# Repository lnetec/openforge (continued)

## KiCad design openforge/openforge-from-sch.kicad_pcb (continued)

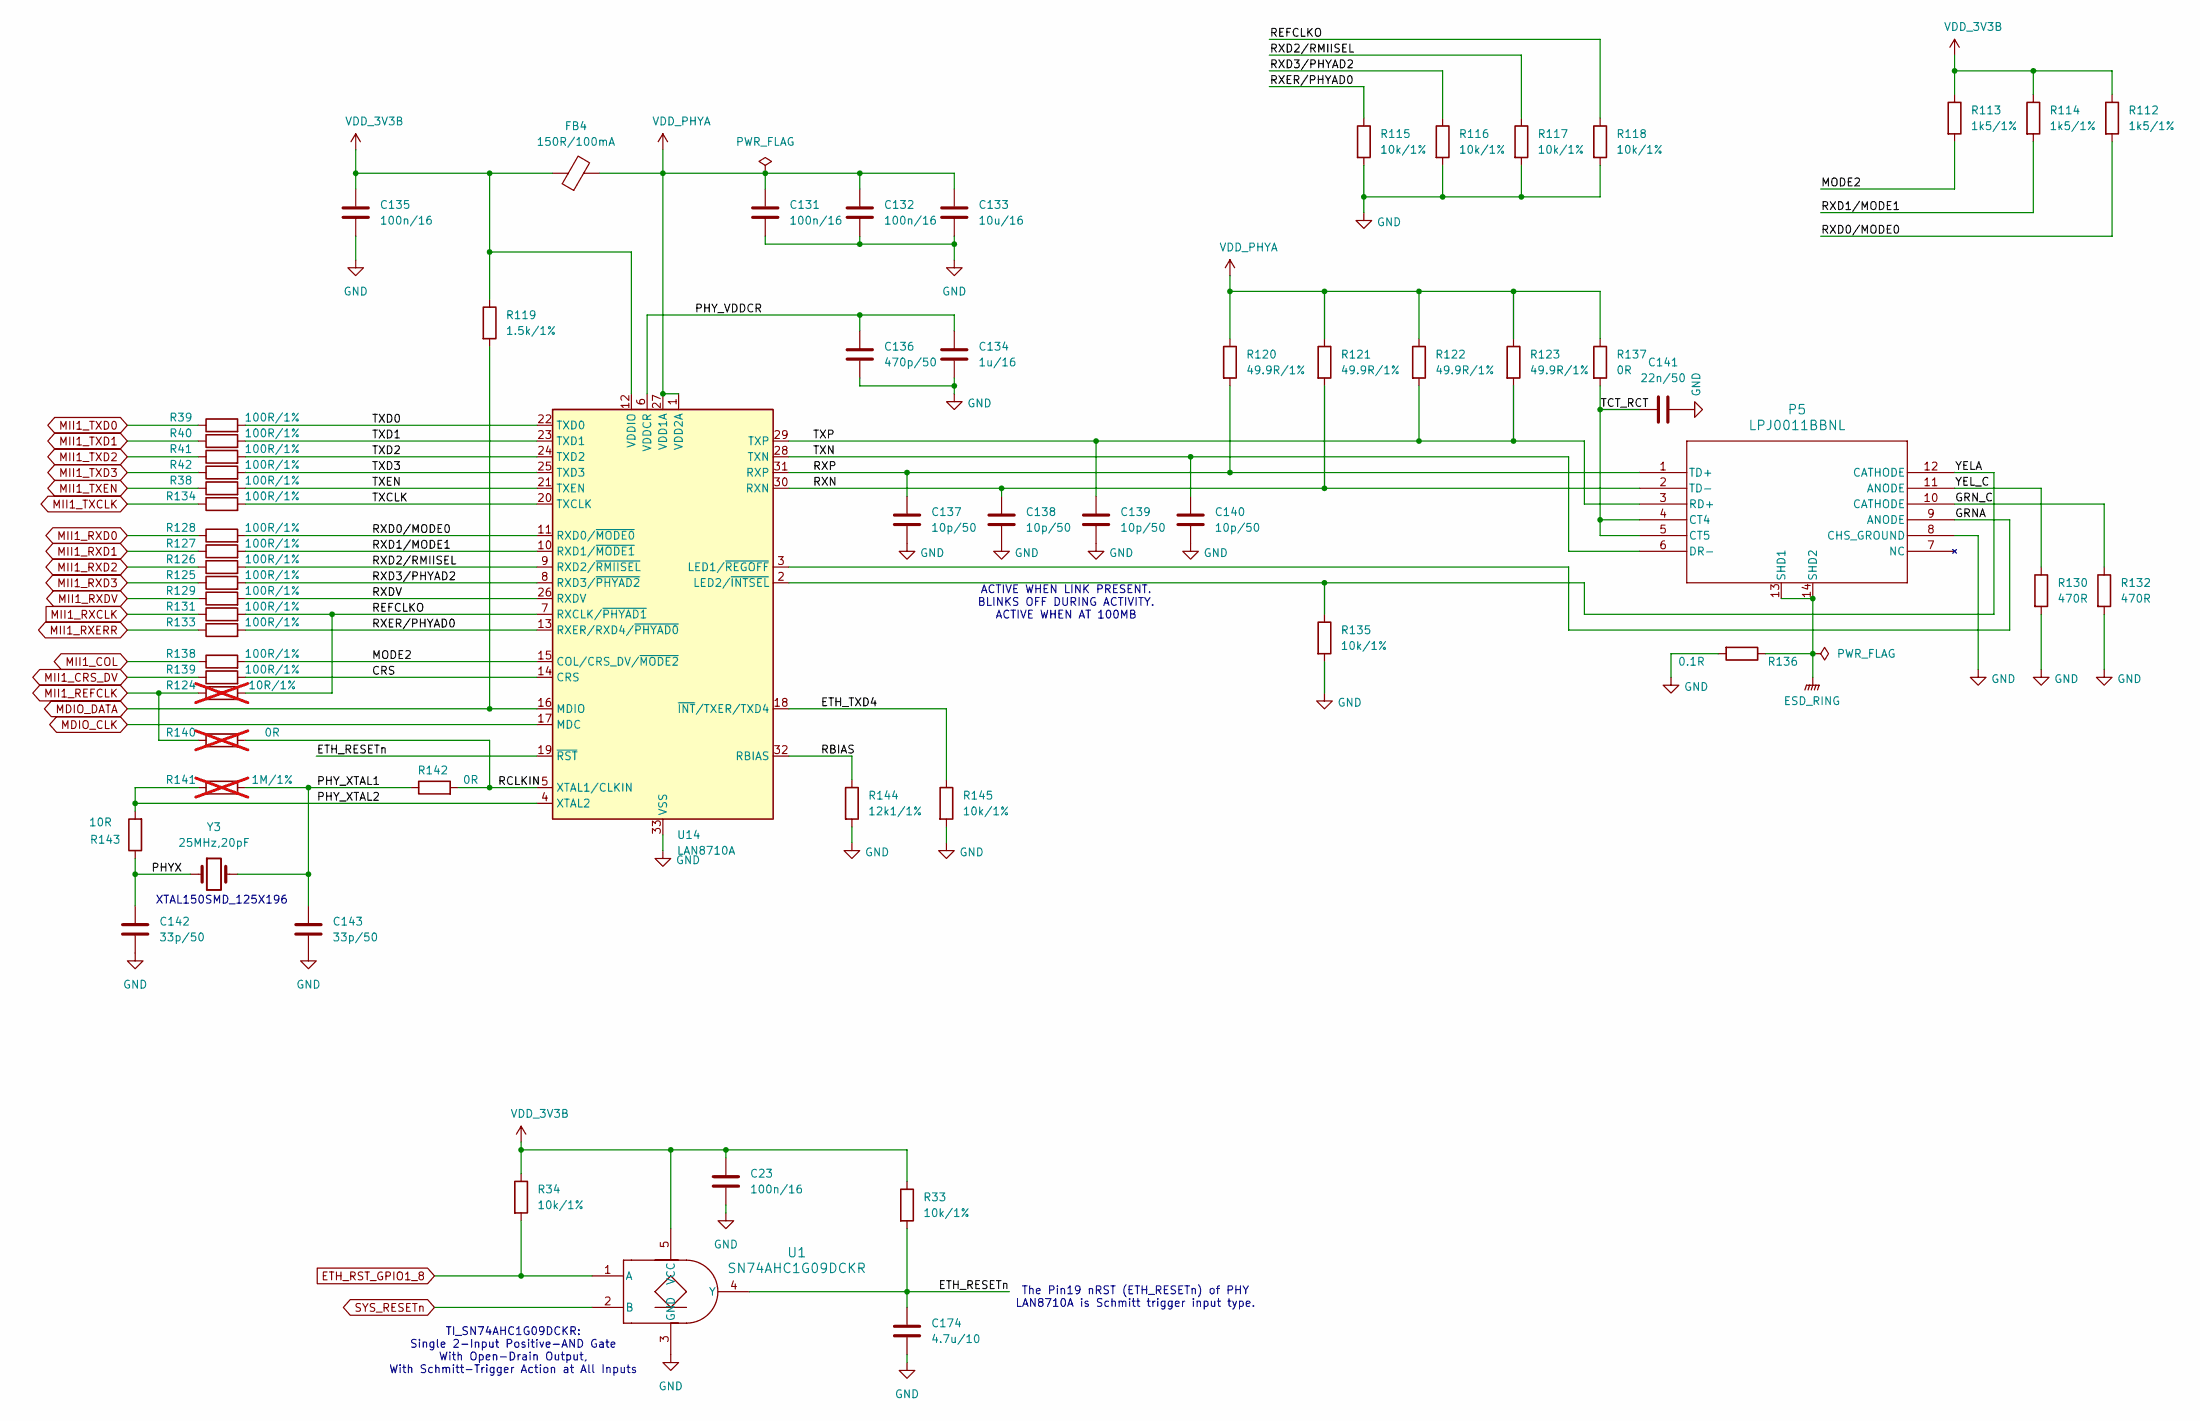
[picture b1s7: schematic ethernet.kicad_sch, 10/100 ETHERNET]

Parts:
C23, C131, C132, C135: 100n/16; C_0402_1005Metric
C133: 10u/16; C_0805_2012Metric
C134: 1u/16; C_0402_1005Metric
C136: 470p/50; C_0402_1005Metric
C137, C138, C139, C140: 10p/50; C_0402_1005Metric
C141: 22n/50; C_0402_1005Metric
C142, C143: 33p/50; C_0402_1005Metric
C174: 4.7u/10; C_0402_1005Metric
FB4: 150R/100mA; L_0805_2012Metric
P5: LPJ0011BBNL; LPJ0011BBNL_LPP
R33, R34, R115, R116, R117, R118, R135, R145: 10k/1%; R_0402_1005Metric
R38, R39, R40, R41, R42, R125, R126, R127, R128, R129, R131, R133, R134, R138, R139: 100R/1%; R_0402_1005Metric
R112, R113, R114: 1k5/1%; R_0402_1005Metric
R119: 1.5k/1%; R_0402_1005Metric
R120, R121, R122, R123: 49.9R/1%; R_0402_1005Metric
R124: 10R/1%; R_0402_1005Metric; not fitted
R130, R132: 470R; R_0402_1005Metric
R136: 0.1R; R_0402_1005Metric
R137, R142: 0R; R_0402_1005Metric
R140: 0R; R_0402_1005Metric; not fitted
R141: 1M/1%; R_0402_1005Metric; not fitted
R143: 10R; R_0402_1005Metric
R144: 12k1/1%; R_0402_1005Metric
U1: SN74AHC1G09DCKR; DCK0005A_L
U14: LAN8710A; QFN-32-1EP_5x5mm_P0.5mm_EP3.3x3.3mm_ThermalVias
Y3: 25MHz,20pF; Crystal_SMD_Abracon_ABM7-2Pin_6.0x3.5mm

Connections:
/Ethernet/CRS: R139.2, U14.14 (CRS)
/Ethernet/ETH_RESETn: C174.1, R33.2, U1.4 (Y), U14.19 (~RST)
/Ethernet/ETH_TXD4: R145.1, U14.18 (~INT/TXER/TXD4)
/Ethernet/GRNA: P5.9 (ANODE), U14.3 (LED1/~REGOFF)
/Ethernet/GRN_C: P5.10 (CATHODE), R132.1
/Ethernet/MODE2: R113.2, R138.2, U14.15 (COL/CRS_DV/~MODE2)
/Ethernet/PHYX: C142.1, R143.1, Y3.1
/Ethernet/PHY_VDDCR: C134.1, C136.1, U14.6 (VDDCR)
/Ethernet/PHY_XTAL1: C143.1, R141.2, R142.1, Y3.2
/Ethernet/PHY_XTAL2: R141.1, R143.2, U14.4 (XTAL2)
/Ethernet/RBIAS: R144.1, U14.32 (RBIAS)
/Ethernet/RCLKIN: R140.2, R142.2, U14.5 (XTAL1/CLKIN)
/Ethernet/REFCLKO: R118.1, R124.2, R131.2, U14.7 (RXCLK/~PHYAD1)
/Ethernet/RXD0/MODE0: R112.2, R128.2, U14.11 (RXD0/~MODE0)
/Ethernet/RXD1/MODE1: R114.2, R127.2, U14.10 (RXD1/~MODE1)
/Ethernet/RXD2/RMIISEL: R117.1, R126.2, U14.9 (RXD2/~RMIISEL)
/Ethernet/RXD3/PHYAD2: R116.1, R125.2, U14.8 (RXD3/~PHYAD2)
/Ethernet/RXDV: R129.2, U14.26 (RXDV)
/Ethernet/RXER/PHYAD0: R115.1, R133.2, U14.13 (RXER/RXD4/~PHYAD0)
/Ethernet/RXN: C138.1, P5.2 (TD-), R121.2, U14.30 (RXN)
/Ethernet/RXP: C137.1, P5.1 (TD+), R120.2, U14.31 (RXP)
/Ethernet/TCT_RCT: C141.1, P5.4 (CT4), P5.5 (CT5), R137.2
/Ethernet/TXCLK: R134.2, U14.20 (TXCLK)
/Ethernet/TXD0: R39.2, U14.22 (TXD0)
/Ethernet/TXD1: R40.2, U14.23 (TXD1)
/Ethernet/TXD2: R41.2, U14.24 (TXD2)
/Ethernet/TXD3: R42.2, U14.25 (TXD3)
/Ethernet/TXEN: R38.2, U14.21 (TXEN)
/Ethernet/TXN: C140.1, P5.6 (DR-), U14.28 (TXN)
/Ethernet/TXP: C139.1, P5.3 (RD+), R122.2, R123.2, U14.29 (TXP)
/Ethernet/YELA: P5.12 (CATHODE), R135.1, U14.2 (LED2/~INTSEL)
/Ethernet/YEL_C: P5.11 (ANODE), R130.1
ESD_RING: P5.13 (SHD1), P5.14 (SHD2), R136.1
ETH_RST_GPIO1_8: R34.2, U1.1 (A); also elsewhere on the board
GND: C23.2, C131.2, C132.2, C133.2, C134.2, C135.2, C136.2, C137.2, C138.2, C139.2, C140.2, C141.2, C142.2, C143.2, C174.2, P5.8 (CHS_GROUND), R115.2, R116.2, R117.2, R118.2, R130.2, R132.2, R135.2, R136.2, R144.2, R145.2, U1.3 (GND), U14.33 (VSS); also elsewhere on the board
MDIO_CLK: U14.17 (MDC); also elsewhere on the board
MDIO_DATA: R119.2, U14.16 (MDIO); also elsewhere on the board
MII1_COL: R138.1; also elsewhere on the board
MII1_CRS_DV: R139.1; also elsewhere on the board
MII1_REFCLK: R124.1, R140.1; also elsewhere on the board
MII1_RXCLK: R131.1; also elsewhere on the board
MII1_RXD0: R128.1; also elsewhere on the board
MII1_RXD1: R127.1; also elsewhere on the board
MII1_RXD2: R126.1; also elsewhere on the board
MII1_RXD3: R125.1; also elsewhere on the board
MII1_RXDV: R129.1; also elsewhere on the board
MII1_RXERR: R133.1; also elsewhere on the board
MII1_TXCLK: R134.1; also elsewhere on the board
MII1_TXD0: R39.1; also elsewhere on the board
MII1_TXD1: R40.1; also elsewhere on the board
MII1_TXD2: R41.1; also elsewhere on the board
MII1_TXD3: R42.1; also elsewhere on the board
MII1_TXEN: R38.1; also elsewhere on the board
SYS_RESETn: U1.2 (B); also elsewhere on the board
VDD_3V3B: C23.1, C135.1, FB4.1, R33.1, R34.1, R112.1, R113.1, R114.1, R119.1, U1.5 (VCC), U14.12 (VDDIO); also elsewhere on the board
VDD_PHYA: C131.1, C132.1, C133.1, FB4.2, R120.1, R121.1, R122.1, R123.1, R137.1, U14.1 (VDD2A), U14.27 (VDD1A)

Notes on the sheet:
The Pin19 nRST (ETH_RESETn) of PHY LAN8710A is Schmitt trigger input type.
TI_SN74AHC1G09DCKR: Single 2-Input Positive-AND Gate With Open-Drain Output, With Schmitt-Trigger Action at All Inputs
ACTIVE WHEN LINK PRESENT. BLINKS OFF DURING ACTIVITY. ACTIVE WHEN AT 100MB
XTAL150SMD_125X196

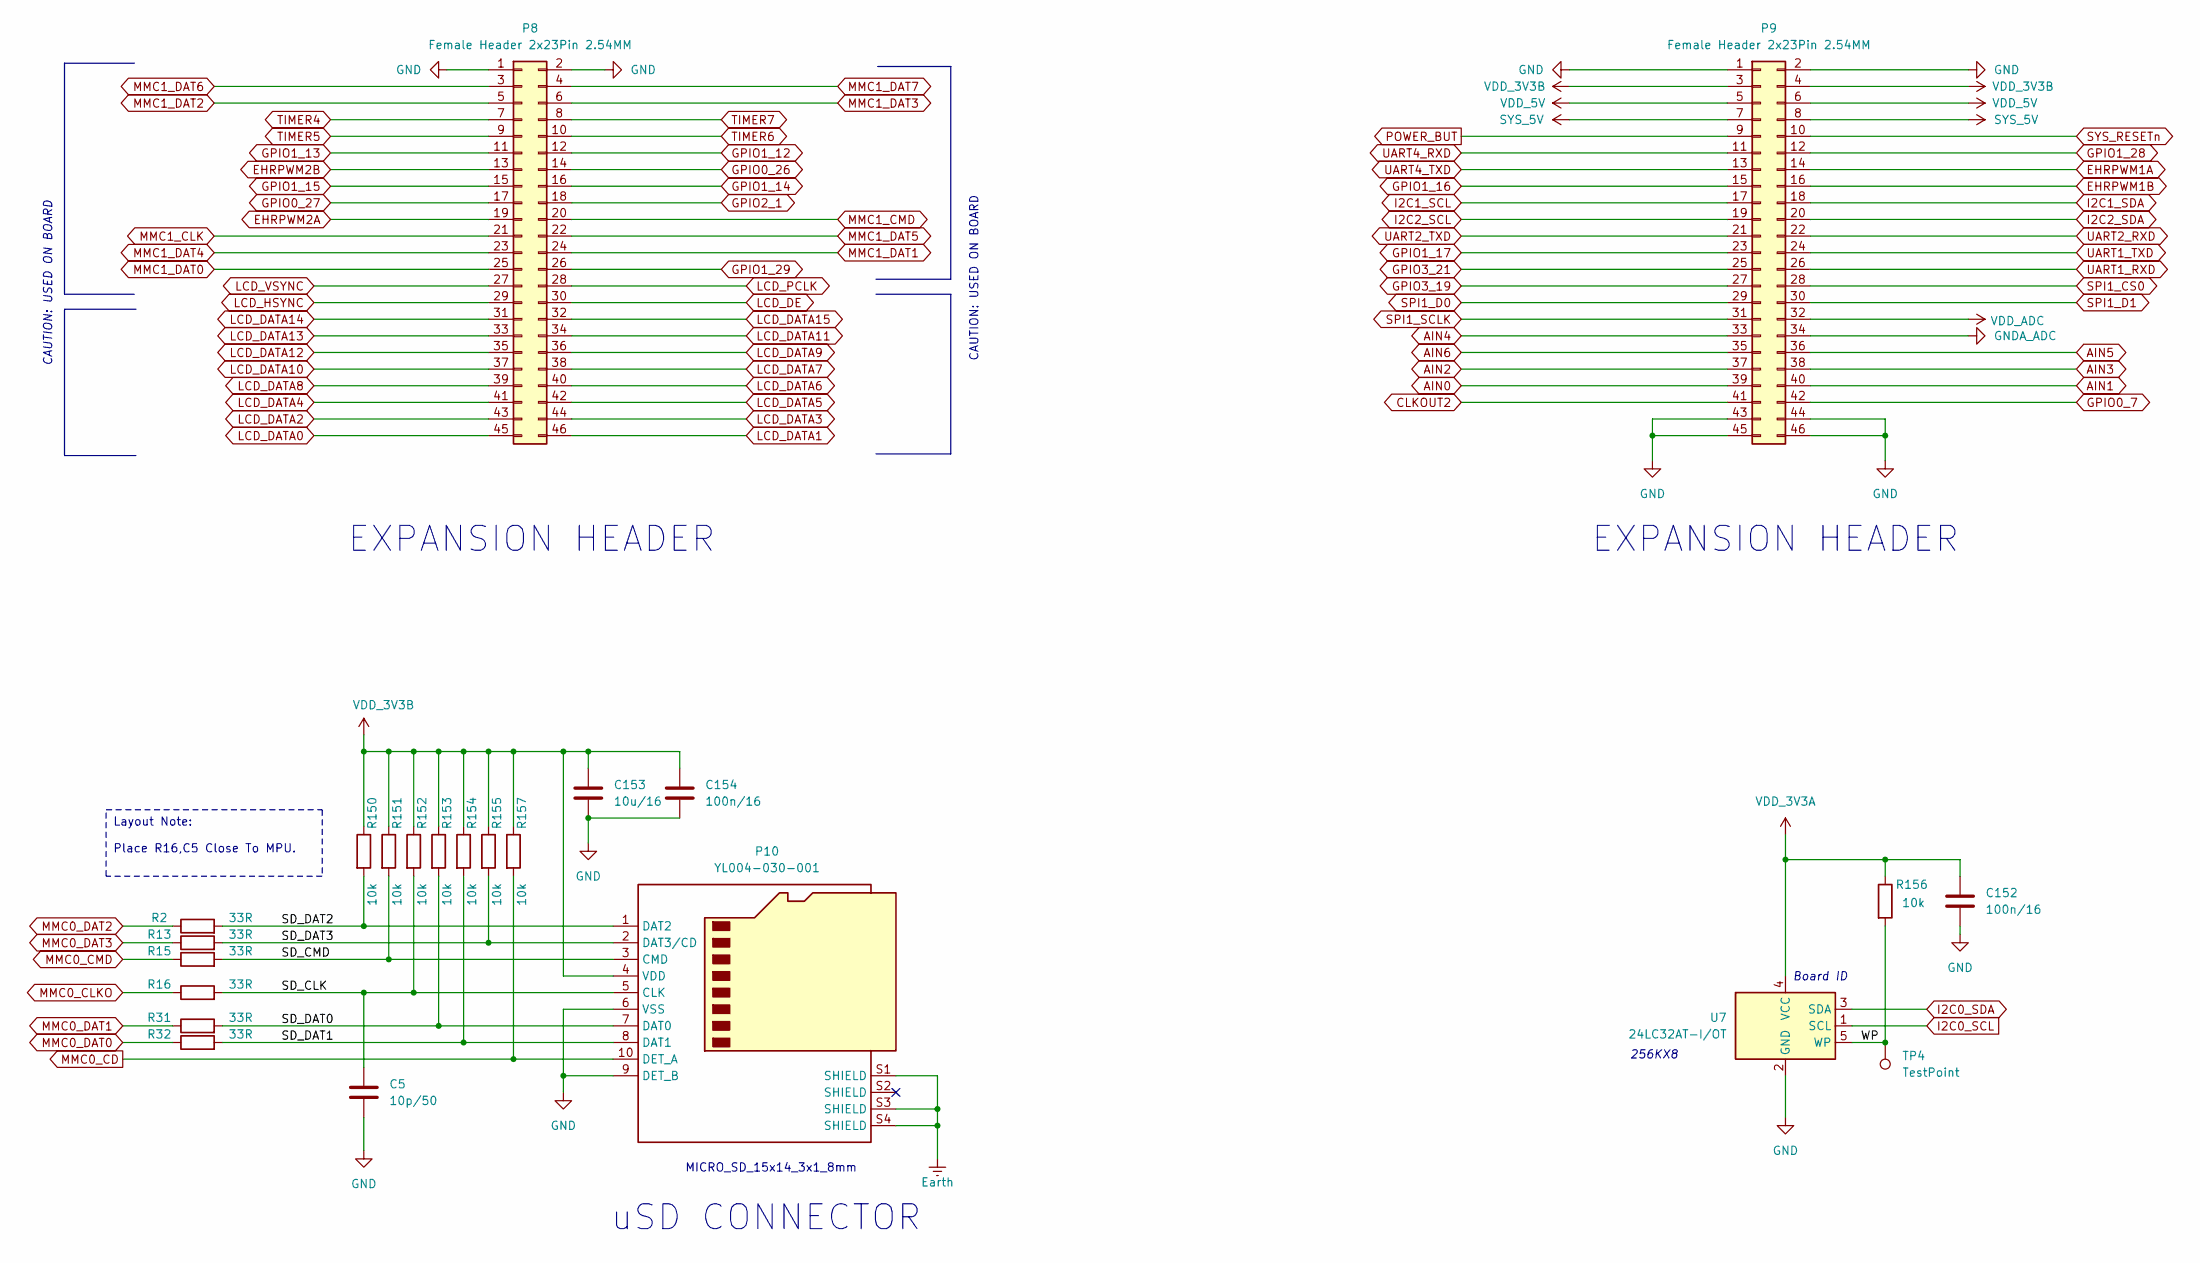
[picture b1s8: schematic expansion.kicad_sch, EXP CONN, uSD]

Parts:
C5: 10p/50; C_0402_1005Metric
C152, C154: 100n/16; C_0402_1005Metric
C153: 10u/16; C_0805_2012Metric
P8, P9: Female Header 2x23Pin 2.54MM; PinHeader_2x23_P2.54mm_Vertical
P10: YL004-030-001; yl004-030-001
R2, R13, R15, R16, R31, R32: 33R; R_0402_1005Metric
R150, R151, R152, R153, R154, R155, R156, R157: 10k; R_0402_1005Metric
TP4: TestPoint; TestPoint_Pad_1.5x1.5mm
U7: 24LC32AT-I/OT; SOT-23-5

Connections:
/Expansion Headers, uSD and EEPROM/SD_CLK: C5.1, P10.5 (CLK), R16.2, R152.2
/Expansion Headers, uSD and EEPROM/SD_CMD: P10.3 (CMD), R15.2, R151.2
/Expansion Headers, uSD and EEPROM/SD_DAT0: P10.7 (DAT0), R31.2, R153.2
/Expansion Headers, uSD and EEPROM/SD_DAT1: P10.8 (DAT1), R32.2, R154.2
/Expansion Headers, uSD and EEPROM/SD_DAT2: P10.1 (DAT2), R2.2, R150.2
/Expansion Headers, uSD and EEPROM/SD_DAT3: P10.2 (DAT3/CD), R13.2, R155.2
/Expansion Headers, uSD and EEPROM/WP: R156.2, TP4.1, U7.5 (WP)
AIN0: P9.39; also elsewhere on the board
AIN1: P9.40; also elsewhere on the board
AIN2: P9.37; also elsewhere on the board
AIN3: P9.38; also elsewhere on the board
AIN4: P9.33; also elsewhere on the board
AIN5: P9.36; also elsewhere on the board
AIN6: P9.35; also elsewhere on the board
CLKOUT2: P9.41; also elsewhere on the board
EHRPWM1A: P9.14; also elsewhere on the board
EHRPWM1B: P9.16; also elsewhere on the board
EHRPWM2A: P8.19; also elsewhere on the board
EHRPWM2B: P8.13; also elsewhere on the board
Earth: P10.S1 (SHIELD), P10.S3 (SHIELD), P10.S4 (SHIELD); also elsewhere on the board
GND: C5.2, C152.2, C153.2, C154.2, P8.1, P8.2, P9.1, P9.2, P9.43, P9.44, P9.45, P9.46, P10.6 (VSS), P10.9 (DET_B), U7.2 (GND); also elsewhere on the board
GNDA_ADC: P9.34; also elsewhere on the board
GPIO0_7: P9.42; also elsewhere on the board
GPIO0_26: P8.14; also elsewhere on the board
GPIO0_27: P8.17; also elsewhere on the board
GPIO1_12: P8.12; also elsewhere on the board
GPIO1_13: P8.11; also elsewhere on the board
GPIO1_14: P8.16; also elsewhere on the board
GPIO1_15: P8.15; also elsewhere on the board
GPIO1_16: P9.15; also elsewhere on the board
GPIO1_17: P9.23; also elsewhere on the board
GPIO1_28: P9.12; also elsewhere on the board
GPIO1_29: P8.26; also elsewhere on the board
GPIO2_1: P8.18; also elsewhere on the board
GPIO3_19: P9.27; also elsewhere on the board
GPIO3_21: P9.25; also elsewhere on the board
I2C0_SCL: U7.1 (SCL); also elsewhere on the board
I2C0_SDA: U7.3 (SDA); also elsewhere on the board
I2C1_SCL: P9.17; also elsewhere on the board
I2C1_SDA: P9.18; also elsewhere on the board
I2C2_SCL: P9.19; also elsewhere on the board
I2C2_SDA: P9.20; also elsewhere on the board
LCD_DATA0: P8.45; also elsewhere on the board
LCD_DATA1: P8.46; also elsewhere on the board
LCD_DATA2: P8.43; also elsewhere on the board
LCD_DATA3: P8.44; also elsewhere on the board
LCD_DATA4: P8.41; also elsewhere on the board
LCD_DATA5: P8.42; also elsewhere on the board
LCD_DATA6: P8.40; also elsewhere on the board
LCD_DATA7: P8.38; also elsewhere on the board
LCD_DATA8: P8.39; also elsewhere on the board
LCD_DATA9: P8.36; also elsewhere on the board
LCD_DATA10: P8.37; also elsewhere on the board
LCD_DATA11: P8.34; also elsewhere on the board
LCD_DATA12: P8.35; also elsewhere on the board
LCD_DATA13: P8.33; also elsewhere on the board
LCD_DATA14: P8.31; also elsewhere on the board
LCD_DATA15: P8.32; also elsewhere on the board
LCD_DE: P8.30; also elsewhere on the board
LCD_HSYNC: P8.29; also elsewhere on the board
LCD_PCLK: P8.28; also elsewhere on the board
LCD_VSYNC: P8.27; also elsewhere on the board
MMC0_CD: P10.10 (DET_A), R157.2; also elsewhere on the board
MMC0_CLKO: R16.1; also elsewhere on the board
MMC0_CMD: R15.1; also elsewhere on the board
MMC0_DAT0: R32.1; also elsewhere on the board
MMC0_DAT1: R31.1; also elsewhere on the board
MMC0_DAT2: R2.1; also elsewhere on the board
MMC0_DAT3: R13.1; also elsewhere on the board
MMC1_CLK: P8.21; also elsewhere on the board
MMC1_CMD: P8.20; also elsewhere on the board
MMC1_DAT0: P8.25; also elsewhere on the board
MMC1_DAT1: P8.24; also elsewhere on the board
MMC1_DAT2: P8.5; also elsewhere on the board
MMC1_DAT3: P8.6; also elsewhere on the board
MMC1_DAT4: P8.23; also elsewhere on the board
MMC1_DAT5: P8.22; also elsewhere on the board
MMC1_DAT6: P8.3; also elsewhere on the board
MMC1_DAT7: P8.4; also elsewhere on the board
POWER_BUT: P9.9; also elsewhere on the board
SPI1_CS0: P9.28; also elsewhere on the board
SPI1_D0: P9.29; also elsewhere on the board
SPI1_D1: P9.30; also elsewhere on the board
SPI1_SCLK: P9.31; also elsewhere on the board
SYS_5V: P9.7, P9.8; also elsewhere on the board
SYS_RESETn: P9.10; also elsewhere on the board
TIMER4: P8.7; also elsewhere on the board
TIMER5: P8.9; also elsewhere on the board
TIMER6: P8.10; also elsewhere on the board
TIMER7: P8.8; also elsewhere on the board
UART1_RXD: P9.26; also elsewhere on the board
UART1_TXD: P9.24; also elsewhere on the board
UART2_RXD: P9.22; also elsewhere on the board
UART2_TXD: P9.21; also elsewhere on the board
UART4_RXD: P9.11; also elsewhere on the board
UART4_TXD: P9.13; also elsewhere on the board
VDD_3V3A: C152.1, R156.1, U7.4 (VCC); also elsewhere on the board
VDD_3V3B: C153.1, C154.1, P9.3, P9.4, P10.4 (VDD), R150.1, R151.1, R152.1, R153.1, R154.1, R155.1, R157.1; also elsewhere on the board
VDD_5V: P9.5, P9.6; also elsewhere on the board
VDD_ADC: P9.32; also elsewhere on the board

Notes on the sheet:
Layout Note: Place R16,C5 Close To MPU.
uSD CONNECTOR
Board ID
EXPANSION HEADER
MICRO_SD_15x14_3x1_8mm
CAUTION: USED ON BOARD
256KX8

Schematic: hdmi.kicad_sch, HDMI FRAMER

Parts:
C144, C145, C146, C147, C148, C149, C150, C151: 2.2u/10; C_0402_1005Metric
C156, C157, C160, C161, C162, C163, C164, C165, C166, C167, C168, C169, C170, C171, C172, C173: 47p/50; C_0402_1005Metric
D6, D7: TPD4S009DGSR; TSSOP-10_3x3mm_P0.5mm
D8: RB751V40,115; D_SOD-323F
FB5: 150R,800mA; L_0805_2012Metric
P6: 10118241-001RLF; CONN_10118241-001RLF_AMP
R146, R147: 1k5; R_0402_1005Metric
R148, R158: 10k; R_0402_1005Metric
R149: 0R; R_0402_1005Metric
R166: 27k; R_0402_1005Metric
RT1: RXEF010; FUS_RXEF010_TYCO_TYC
U11: TDA19988BHN_C1_557; QFN50P900X900X100-65N; PARTREV 3

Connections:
12MHZ: U11.27 (OSC_IN/AP3); also elsewhere on the board
/HDMI Interface/DVI_+5V: P6.19 (+5V), R146.1, R147.1, RT1.1
/HDMI Interface/HDMI_CEC: D8.1 (K), P6.15 (CEC), U11.30 (CEC)
/HDMI Interface/HDMI_DSCL: P6.17 (SCL), R147.2, U11.33 (DSCL)
/HDMI Interface/HDMI_DSDA: P6.18 (SDA), R146.2, U11.32 (DSDA)
/HDMI Interface/HDMI_HPD: P6.1 (HPD/HEAC-), U11.31 (HPD)
/HDMI Interface/HDMI_SWING: R148.2, U11.34 (EXT_SWING)
/HDMI Interface/HDMI_TX0+: D6.1 (D1+), P6.9 (D0+), U11.40 (TX0+)
/HDMI Interface/HDMI_TX0-: D6.2 (D1-), P6.11 (D0-), U11.39 (TX0-)
/HDMI Interface/HDMI_TX1+: D7.4 (D2+), P6.6 (D1+), U11.43 (TX1+)
/HDMI Interface/HDMI_TX1-: D7.5 (D2-), P6.8 (D1-), U11.42 (TX1-)
/HDMI Interface/HDMI_TX2+: D7.1 (D1+), P6.3 (D2+), U11.45 (TX2+)
/HDMI Interface/HDMI_TX2-: D7.2 (D1-), P6.5 (D2-), U11.44 (TX2-)
/HDMI Interface/HDMI_TXC+: D6.4 (D2+), P6.12 (CK+), U11.38 (TXC+)
/HDMI Interface/HDMI_TXC-: D6.5 (D2-), P6.14 (CK-), U11.37 (TXC-)
Earth: P6.20 (MTG1), P6.21 (MTG1), P6.22 (MTG1), P6.23 (MTG1); also elsewhere on the board
GND: C144.2, C145.2, C146.2, C147.2, C148.2, C149.2, C150.2, C151.2, C156.2, C157.2, C160.2, C161.2, C162.2, C163.2, C164.2, C165.2, C166.2, C167.2, C168.2, C169.2, C170.2, C171.2, C172.2, C173.2, D6.3 (GND), D6.8 (VCC), D7.3 (GND), D7.8 (VCC), P6.4 (D2S), P6.7 (D1S), P6.10 (D0S), P6.13 (CKS), P6.16 (GND), R148.1, R149.2, U11.8 (VPB[1]), U11.9 (VPB[0]), U11.16 (VPC[2]), U11.17 (VPC[1]), U11.18 (VPC[0]), U11.19 (VPP), U11.53 (A0_I2C), U11.54 (A1_I2C), U11.61 (VPA[2]), U11.62 (VPA[1]), U11.63 (VPA[0]), U11.65 (EXP/GND); also elsewhere on the board
HDMI_1V8: C144.1, C145.1, C146.1, C147.1, C148.1, C149.1, C150.1, C151.1, FB5.2, U11.5 (VDDDC), U11.14 (VDDD(IO)(1V8)), U11.29 (VDDDC__1), U11.35 (VDDA(1V8)), U11.36 (VDDA(TX)(1V8)), U11.41 (VDDA(TX)(1V8)__1), U11.46 (VDDA(TX)(1V8)__2), U11.47 (VDDA(PLL)(1V8)), U11.48 (VDDA(PLL)(1V8)__1), U11.55 (VDDD(IO)(1V8)__1)
HDMI_INT: R158.2, U11.50 (INT); also elsewhere on the board
I2C0_SCL: U11.52 (CSCL); also elsewhere on the board
I2C0_SDA: U11.51 (CSDA); also elsewhere on the board
LCD_DATA0: C173.1, U11.15 (VPC[3]); also elsewhere on the board
LCD_DATA1: C171.1, U11.13 (VPC[4]); also elsewhere on the board
LCD_DATA2: C172.1, U11.12 (VPC[5]); also elsewhere on the board
LCD_DATA3: C170.1, U11.11 (VPC[6]); also elsewhere on the board
LCD_DATA4: C169.1, U11.10 (VPC[7]); also elsewhere on the board
LCD_DATA5: C168.1, U11.7 (VPB[2]); also elsewhere on the board
LCD_DATA6: C167.1, U11.6 (VPB[3]); also elsewhere on the board
LCD_DATA7: C166.1, U11.3 (VPB[4]); also elsewhere on the board
LCD_DATA8: C165.1, U11.2 (VPB[5]); also elsewhere on the board
LCD_DATA9: C164.1, U11.1 (VPB[6]); also elsewhere on the board
LCD_DATA10: C163.1, U11.64 (VPB[7]); also elsewhere on the board
LCD_DATA11: C162.1, U11.60 (VPA[3]); also elsewhere on the board
LCD_DATA12: C161.1, U11.59 (VPA[4]); also elsewhere on the board
LCD_DATA13: C160.1, U11.58 (VPA[5]); also elsewhere on the board
LCD_DATA14: C157.1, U11.57 (VPA[6]); also elsewhere on the board
LCD_DATA15: C156.1, U11.56 (VPA[7]); also elsewhere on the board
LCD_DE: U11.20 (DE/FREF); also elsewhere on the board
LCD_HSYNC: U11.22 (HSYNC/HREF); also elsewhere on the board
LCD_PCLK: U11.4 (PCLK); also elsewhere on the board
LCD_VSYNC: U11.21 (VSYNC/VREF); also elsewhere on the board
unnamed: D8.2 (A), R166.2
unnamed: R149.1, U11.49 (TEST)
SPI1_CS0: U11.25 (AP1); also elsewhere on the board
SPI1_D0: U11.24 (AP0); also elsewhere on the board
SPI1_SCLK: U11.23 (ACLK); also elsewhere on the board
SYS_5V: RT1.2; also elsewhere on the board
VDD_1V8: FB5.1; also elsewhere on the board
VDD_3V3B: R158.1, R166.1; also elsewhere on the board

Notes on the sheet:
McASP0_ACLKX (Pin A13 Mode 0)
McASP0_FSX (Pin B13 Mode 0)
GREEN
RED
BLUE
McASP0_AXR2 (Pin C12 Mode 2)

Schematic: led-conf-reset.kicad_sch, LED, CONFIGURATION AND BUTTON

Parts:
D2, D3, D4, D5: 19-217/BHC-ZL1M2RY/3T; LED_0603_1608Metric
Q1, Q2: DDC114YU-7-F; SOT-363_SC-70-6
R55, R57, R58, R59, R60, R61, R62, R63, R64, R69, R70, R81, R90, R91, R92, R93: 100K/1%; R_0402_1005Metric; not fitted
R56, R65, R66, R67, R68, R80, R82, R83, R84, R85, R86, R87, R88, R89, R94, R95: 100K/1%; R_0402_1005Metric
R71, R72, R73, R74: 2k2/5%; R_0402_1005Metric
R75: 100R/1%; R_0402_1005Metric
R76, R77, R78, R79: 100k; R_0402_1005Metric
S2: KMR231GLFS; KMR2xxG_CNK

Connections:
/LED, Configuration And Reset/LEDAA: D2.2 (A), R72.2
/LED, Configuration And Reset/LEDAC: D2.1 (K), Q1.6 (C1)
/LED, Configuration And Reset/LEDBA: D3.2 (A), R73.2
/LED, Configuration And Reset/LEDBC: D3.1 (K), Q1.3 (C2)
/LED, Configuration And Reset/LEDCA: D4.2 (A), R74.2
/LED, Configuration And Reset/LEDCC: D4.1 (K), Q2.6 (C1)
/LED, Configuration And Reset/LEDDA: D5.2 (A), R71.2
/LED, Configuration And Reset/LEDDC: D5.1 (K), Q2.3 (C2)
GND: Q1.1 (E1), Q1.4 (E2), Q2.1 (E1), Q2.4 (E2), R76.2, R77.2, R78.1, R79.1, R80.1, R81.1, R82.1, R83.1, R84.1, R85.1, R86.1, R87.1, R88.1, R89.1, R90.1, R91.1, R92.1, R93.1, R94.1, R95.1, S2.3 (K), S2.4 (A); also elsewhere on the board
LCD_DATA0: R70.2, R95.2; also elsewhere on the board
LCD_DATA1: R69.2, R94.2; also elsewhere on the board
LCD_DATA2: R68.2, R75.1, R93.2; also elsewhere on the board
LCD_DATA3: R67.2, R92.2; also elsewhere on the board
LCD_DATA4: R66.2, R91.2; also elsewhere on the board
LCD_DATA5: R65.2, R90.2; also elsewhere on the board
LCD_DATA6: R64.2, R89.2; also elsewhere on the board
LCD_DATA7: R63.2, R88.2; also elsewhere on the board
LCD_DATA8: R62.2, R87.2; also elsewhere on the board
LCD_DATA9: R61.2, R86.2; also elsewhere on the board
LCD_DATA10: R60.2, R85.2; also elsewhere on the board
LCD_DATA11: R59.2, R84.2; also elsewhere on the board
LCD_DATA12: R58.2, R83.2; also elsewhere on the board
LCD_DATA13: R57.2, R82.2; also elsewhere on the board
LCD_DATA14: R56.2, R81.2; also elsewhere on the board
LCD_DATA15: R55.2, R80.2; also elsewhere on the board
unnamed: R75.2, S2.1, S2.2
SYS_5V: R71.1, R72.1, R73.1, R74.1; also elsewhere on the board
USR0: Q1.2 (B1), R76.1; also elsewhere on the board
USR1: Q1.5 (B2), R77.1; also elsewhere on the board
USR2: Q2.2 (B1), R78.2; also elsewhere on the board
USR3: Q2.5 (B2), R79.2; also elsewhere on the board
VDD_3V3A: R55.1, R56.1, R57.1, R58.1, R59.1, R60.1, R61.1, R62.1, R63.1, R64.1, R65.1, R66.1, R67.1, R68.1, R69.1, R70.1; also elsewhere on the board

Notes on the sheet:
USR3
USER LEDs
USR0
USR2
uSD BOOT
USR1

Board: 2 copper layers, 413 parts (0 on the bottom side), 334 nets, no tracks yet.

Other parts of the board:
C1, C2, C7, C8, C10, C13: 10u/16; C_0805_2012Metric
C3: 100n/16n; C_0402_1005Metric
C4, C9, C11, C12, C14, C15: 10u/16n; C_0805_2012Metric
C16, C18: 2.2u/10n; C_0402_1005Metric
C17: 2.2u/16; C_0402_1005Metric
C19: 470p/50; C_0402_1005Metric
C20: 100n/16; C_0402_1005Metric
D1: LED; LED_0603_1608Metric
L1, L2, L3: 2.2u/1.3A; L_1008_2520Metric
MTG1, MTG2, MTG3, MTG4: MHOLE; MountingHole_2.5mm_Pad_TopBottom
P1: conn_power_in; PJ-102A_CUD
R1: 100k/1%; R_0402_1005Metric
R3, R4: 1k5/1%; R_0402_1005Metric
R5, R6, R7, R8, R9: 0R; R_0402_1005Metric
R10: 470K/1%; R_0402_1005Metric
R11: 280K/1%; R_0402_1005Metric
R12: 470R/5%; R_0402_1005Metric
S3: SW_MEC_5E; KMR2xxG_CNK
TP1, TP5, TP6, TP7, TP8: TestPoint; TestPoint_Pad_1.5x1.5mm
U2: TPS65217ARSLR; RSL48_4P05X4P05
U4: TL5209DR; D8

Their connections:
/Power Management/PWR_LEDR: D1.1 (K), R12.2
/Power Management/P_L1: L1.1, U2.20 (L1)
/Power Management/P_L2: L2.1, U2.23 (L2)
/Power Management/P_L3: L3.1, U2.31 (L3)
/Power Management/VDCDC1: L1.2, R6.1, U2.19 (VDCDC1)
/Power Management/VLDO1: R5.1, R7.1, R8.1, U2.3 (VLDO1)
Earth: MTG1.1, MTG2.1, MTG3.1, MTG4.1; also elsewhere on the board
GND: C1.2, C2.2, C3.2, C4.2, C7.2, C8.2, C9.1, C10.2, C11.1, C12.1, C13.1, C14.1, C15.1, C16.1, C17.2, C18.1, C19.2, C20.2, P1.2, R10.1, R12.1, S3.1, S3.2, TP1.1, TP8.1, U2.30 (PGND), U2.41 (AGND), U2.49 (EPAD), U4.5 (GND), U4.6 (GND), U4.7 (GND), U4.8 (GND); also elsewhere on the board
I2C0_SCL: R3.1, U2.28 (SCL); also elsewhere on the board
I2C0_SDA: R4.1, U2.27 (SDA); also elsewhere on the board
LDO_PGOOD: U2.46 (LDO_PGOOD); also elsewhere on the board
unnamed: TP5.1, U2.4 (BAT), U2.5 (BAT)
unnamed: TP6.1, U2.6 (BAT_SENSE)
unnamed: C4.1, U2.47 (BYPASS)
unnamed: C3.1, U2.48 (INT_LDO)
unnamed: TP7.1, U2.11 (TS)
unnamed: C19.1, R10.2, R11.1, U4.4 (ADJ/BYP)
PMIC_INT: R1.1, U2.45 (NINT); also elsewhere on the board
PMIC_PGOOD: U2.26 (PGOOD); also elsewhere on the board
PMIC_POWER_EN: U2.9 (PWR_EN); also elsewhere on the board
POWER_BUT: S3.3 (K), S3.4 (A), U2.25 (PB_IN); also elsewhere on the board
SYS_5V: C7.1, C8.1, C10.1, C13.2, C17.1, U2.2 (VINLDO), U2.7 (SYS), U2.8 (SYS), U2.21 (VIN_DCDC1), U2.22 (VIN_DCDC2), U2.32 (VIN_DCDC3), U2.39 (LS1_IN), U2.42 (LS2_IN), U4.2 (IN); also elsewhere on the board
USB_DC: C1.1, U2.12 (USB); also elsewhere on the board
VDDS: R8.2, R9.1; also elsewhere on the board
VDDS_DDR: C9.2, R6.2; also elsewhere on the board
VDD_1V8: C14.2, R9.2, U2.40 (LS1_OUT); also elsewhere on the board
VDD_3V3A: C15.2, R1.2, R3.2, R4.2, U2.43 (LS2_OUT), U4.1 (EN); also elsewhere on the board
VDD_3V3AUX: C18.2, D1.2 (A), U2.1 (VLDO2)
VDD_3V3B: C20.1, R11.2, U4.3 (OUT); also elsewhere on the board
VDD_5V: C2.1, P1.1, U2.10 (AC); also elsewhere on the board
VDD_CORE: C11.2, L3.2, U2.29 (VDCDC3); also elsewhere on the board
VDD_MPU: C12.2, L2.2, U2.24 (VDCDC2); also elsewhere on the board
VIO: R7.2, U2.18 (VIO); also elsewhere on the board
VRTC: C16.2, R5.2; also elsewhere on the board
WAKEUP: U2.13 (NWAKEUP); also elsewhere on the board

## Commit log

2024-06-11 initial release
2024-06-11 remove backups from git tracking
2024-06-12 added footprint associations
2024-06-14 Completed footprint association. Partially placed top side components on PCB
2024-06-19 PCB all layers copied from beaglebone black
2024-06-20 fixed various footprints
2024-06-21 pcb zone fills correction
2024-06-25 modified 0402, 0805 R and C footprints. Removed many PCB errors
2024-06-26 fixed all errors and major warnings
